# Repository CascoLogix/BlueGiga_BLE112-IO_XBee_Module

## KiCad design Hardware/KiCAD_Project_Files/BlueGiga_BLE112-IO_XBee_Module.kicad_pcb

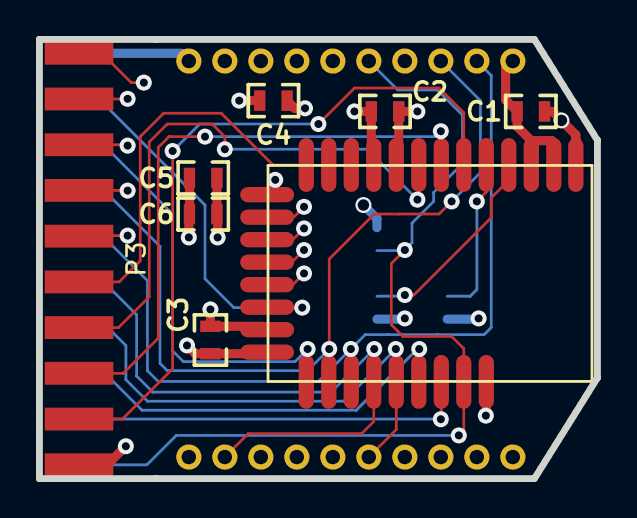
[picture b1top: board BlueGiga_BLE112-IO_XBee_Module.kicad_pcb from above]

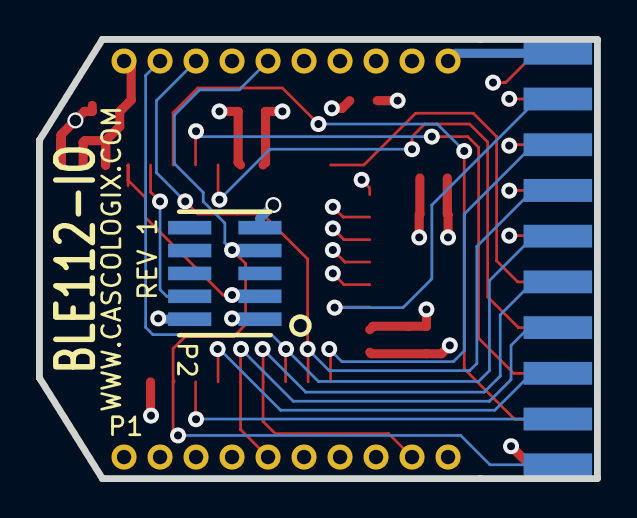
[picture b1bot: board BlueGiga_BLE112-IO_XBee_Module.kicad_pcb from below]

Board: 4 copper layers, 31.0 x 24.4 mm, 10 parts (2 on the bottom side), 22 nets.

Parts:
C1, C2, C3: 1u; C0603
C4, C5: 4.7u; C0603
C6: 0.47u; C0603
P1: XBEE HEADER; HEADER_XBEE
P2: DEBUG; HEADER_50MIL_2R10P_SMT
P3: HEADER_M_2.54MM_2R20P_ST_AU_PTH; HEADER_100MIL_2R20P_EDGE
U1: BLE112-A; BLE112

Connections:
+3V3: C1.1, C2.1, C3.1, C4.1, C5.1, C6.1, P1.1, P2.2, P2.9, P3.1, U1.2, U1.3, U1.9, U1.20
GND: C1.2, C2.2, C3.2, C4.2, C5.2, C6.2, P1.10, P2.1, P3.20, U1.1, U1.10, U1.21, U1.30
P0_0: P3.4, U1.28
P0_1: P3.6, U1.27
P0_2/RX: P1.3, P3.14, U1.23
P0_3/TX: P1.2, P3.12, U1.24
P0_4/CT: P1.16, P3.8, U1.26
P0_5/RT: P1.12, P3.10, U1.25
P0_6: P3.16, U1.22
P0_7: P3.18, U1.19
P1_0: P3.19, U1.18
P1_1: P3.17, U1.17
P1_2: P3.15, U1.16
P1_3: P3.13, U1.15
P1_4: P3.11, U1.14
P1_5: P3.9, U1.13
P1_6: P3.7, U1.8
P1_7: P3.5, U1.7
P2_0: P3.3, U1.6
P2_1: P2.4, U1.5
P2_2: P2.3, U1.4
RESET: P1.5, P2.7, P3.2, U1.29

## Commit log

2015-07-10 First commit.
2015-07-10 Added git ignore
2015-07-29 Rev 1.0 complete. Updated all KiCAD project files and generated gerbers.
2015-08-20 Changed schematic and board layout to conform to BlueGiga's usage of USART1 ALT1.
2015-08-20 Removed outdated gerber files.
